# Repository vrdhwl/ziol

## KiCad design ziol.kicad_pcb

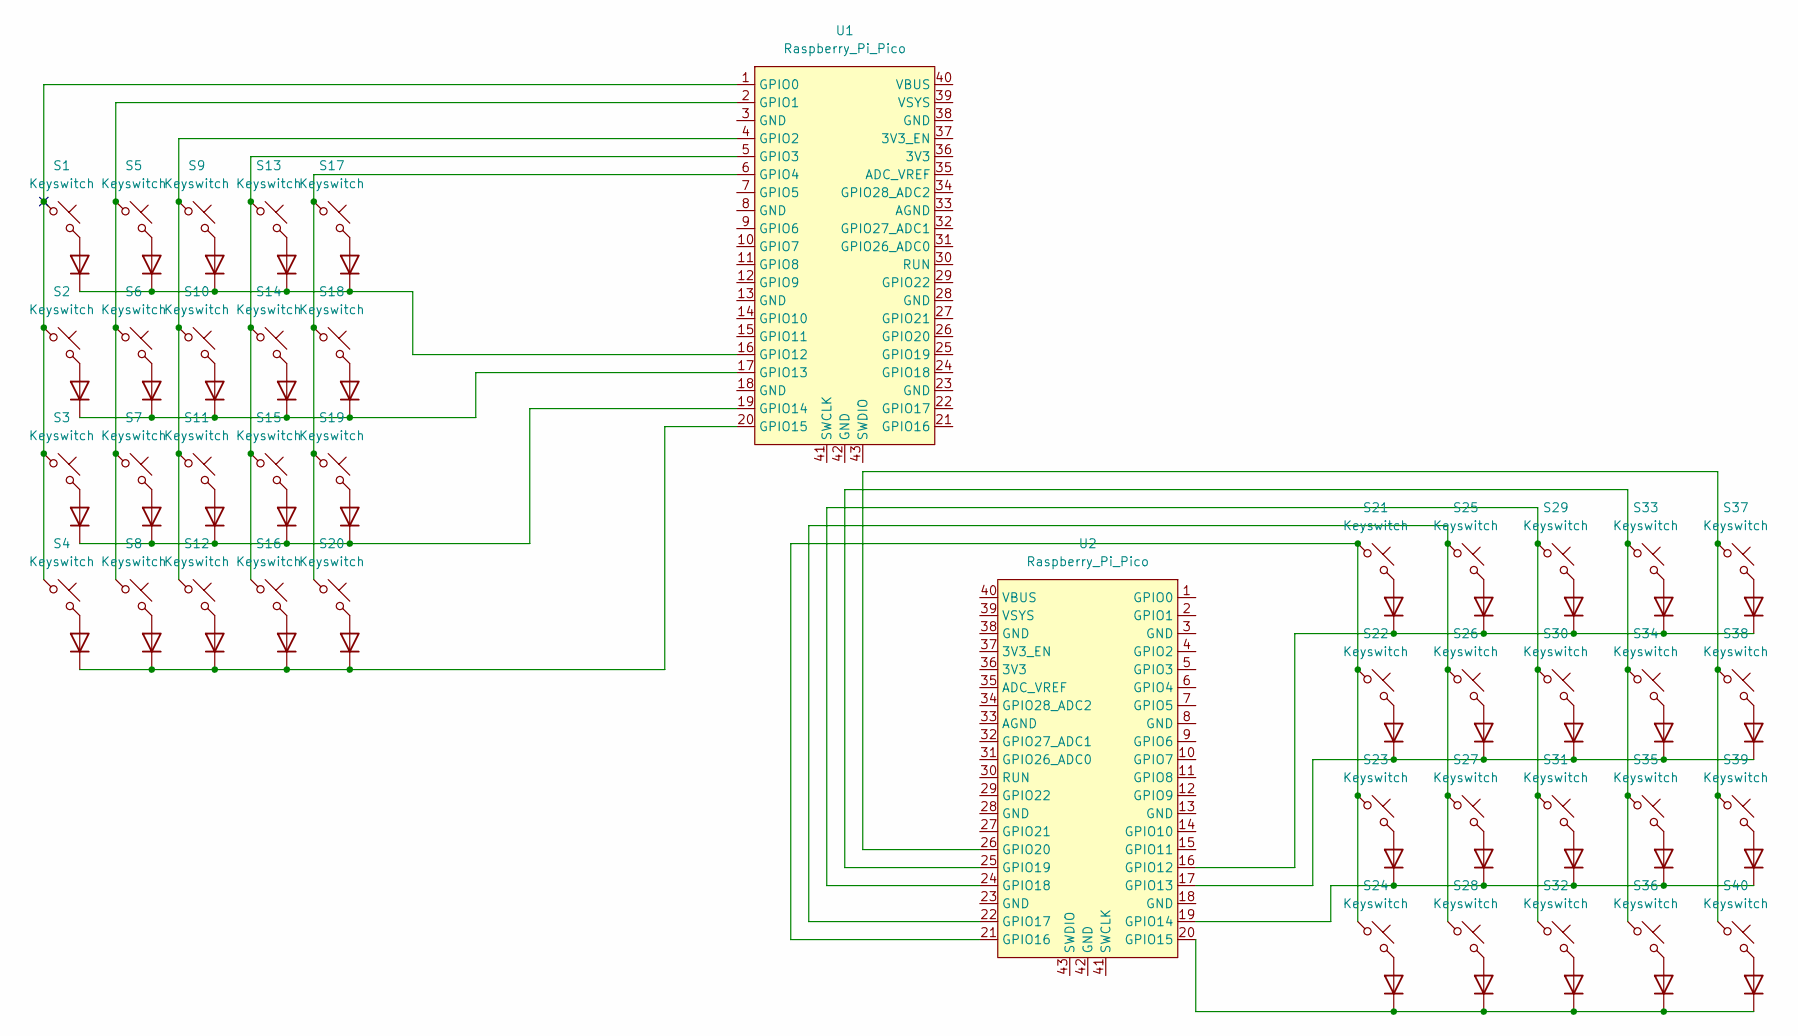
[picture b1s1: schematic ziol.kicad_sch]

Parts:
D1, D2, D3, D4, D5, D6, D7, D8, D9, D10, D11, D12, D13, D14, D15, D16, D17, D18, D19, D20, D21, D22, D23, D24, D25, D26, D27, D28, D29, D30, D31, D32, D33, D34, D35, D36, D37, D38, D39, D40: Diode; Diode_SOD-123
S1, S2, S3, S4, S5, S6, S7, S8, S9, S10, S11, S12, S13, S14, S15, S16, S17, S18, S19, S20, S21, S22, S23, S24, S25, S26, S27, S28, S29, S30, S31, S32, S33, S34, S35, S36, S37, S38, S39, S40: Keyswitch; MX_PCB_1.00u
U1, U2: Raspberry_Pi_Pico

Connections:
unnamed: D1.2 (A), S1.2
unnamed: D1.1 (K), D5.1 (K), D9.1 (K), D13.1 (K), D17.1 (K), U1.16 (GPIO12)
unnamed: D2.2 (A), S2.2
unnamed: D3.2 (A), S3.2
unnamed: D4.2 (A), S4.2
unnamed: D5.2 (A), S5.2
unnamed: D6.2 (A), S6.2
unnamed: D7.2 (A), S7.2
unnamed: D8.2 (A), S8.2
unnamed: D9.2 (A), S9.2
unnamed: D10.2 (A), S10.2
unnamed: D2.1 (K), D6.1 (K), D10.1 (K), D14.1 (K), D18.1 (K), U1.17 (GPIO13)
unnamed: D11.2 (A), S11.2
unnamed: D3.1 (K), D7.1 (K), D11.1 (K), D15.1 (K), D19.1 (K), U1.19 (GPIO14)
unnamed: D12.2 (A), S12.2
unnamed: D4.1 (K), D8.1 (K), D12.1 (K), D16.1 (K), D20.1 (K), U1.20 (GPIO15)
unnamed: D13.2 (A), S13.2
unnamed: D14.2 (A), S14.2
unnamed: D15.2 (A), S15.2
unnamed: D16.2 (A), S16.2
unnamed: D17.2 (A), S17.2
unnamed: D18.2 (A), S18.2
unnamed: D19.2 (A), S19.2
unnamed: D20.2 (A), S20.2
unnamed: D21.2 (A), S21.2
unnamed: D21.1 (K), D25.1 (K), D29.1 (K), D33.1 (K), D37.1 (K), U2.16 (GPIO12)
unnamed: D22.2 (A), S22.2
unnamed: D22.1 (K), D26.1 (K), D30.1 (K), D34.1 (K), D38.1 (K), U2.17 (GPIO13)
unnamed: D23.2 (A), S23.2
unnamed: D23.1 (K), D27.1 (K), D31.1 (K), D35.1 (K), D39.1 (K), U2.19 (GPIO14)
unnamed: D24.2 (A), S24.2
unnamed: D24.1 (K), D28.1 (K), D32.1 (K), D36.1 (K), D40.1 (K), U2.20 (GPIO15)
unnamed: D25.2 (A), S25.2
unnamed: D26.2 (A), S26.2
unnamed: D27.2 (A), S27.2
unnamed: D28.2 (A), S28.2
unnamed: D29.2 (A), S29.2
unnamed: D30.2 (A), S30.2
unnamed: D31.2 (A), S31.2
unnamed: D32.2 (A), S32.2
unnamed: D33.2 (A), S33.2
unnamed: D34.2 (A), S34.2
unnamed: D35.2 (A), S35.2
unnamed: D36.2 (A), S36.2
unnamed: D37.2 (A), S37.2
unnamed: D38.2 (A), S38.2
unnamed: D39.2 (A), S39.2
unnamed: D40.2 (A), S40.2
unnamed: S5.1, S6.1, S7.1, S8.1, U1.2 (GPIO1)
unnamed: S9.1, S10.1, S11.1, S12.1, U1.4 (GPIO2)
unnamed: S13.1, S14.1, S15.1, S16.1, U1.5 (GPIO3)
unnamed: S17.1, S18.1, S19.1, S20.1, U1.6 (GPIO4)
unnamed: S21.1, S22.1, S23.1, S24.1, U2.21 (GPIO16)
unnamed: S25.1, S26.1, S27.1, S28.1, U2.22 (GPIO17)
unnamed: S29.1, S30.1, S31.1, S32.1, U2.24 (GPIO18)
unnamed: S33.1, S34.1, S35.1, S36.1, U2.25 (GPIO19)
unnamed: S37.1, S38.1, S39.1, S40.1, U2.26 (GPIO20)

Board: 2 copper layers, 82 parts (0 on the bottom side), 57 nets, no tracks yet.

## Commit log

2025-02-26 Piece De Revolution
